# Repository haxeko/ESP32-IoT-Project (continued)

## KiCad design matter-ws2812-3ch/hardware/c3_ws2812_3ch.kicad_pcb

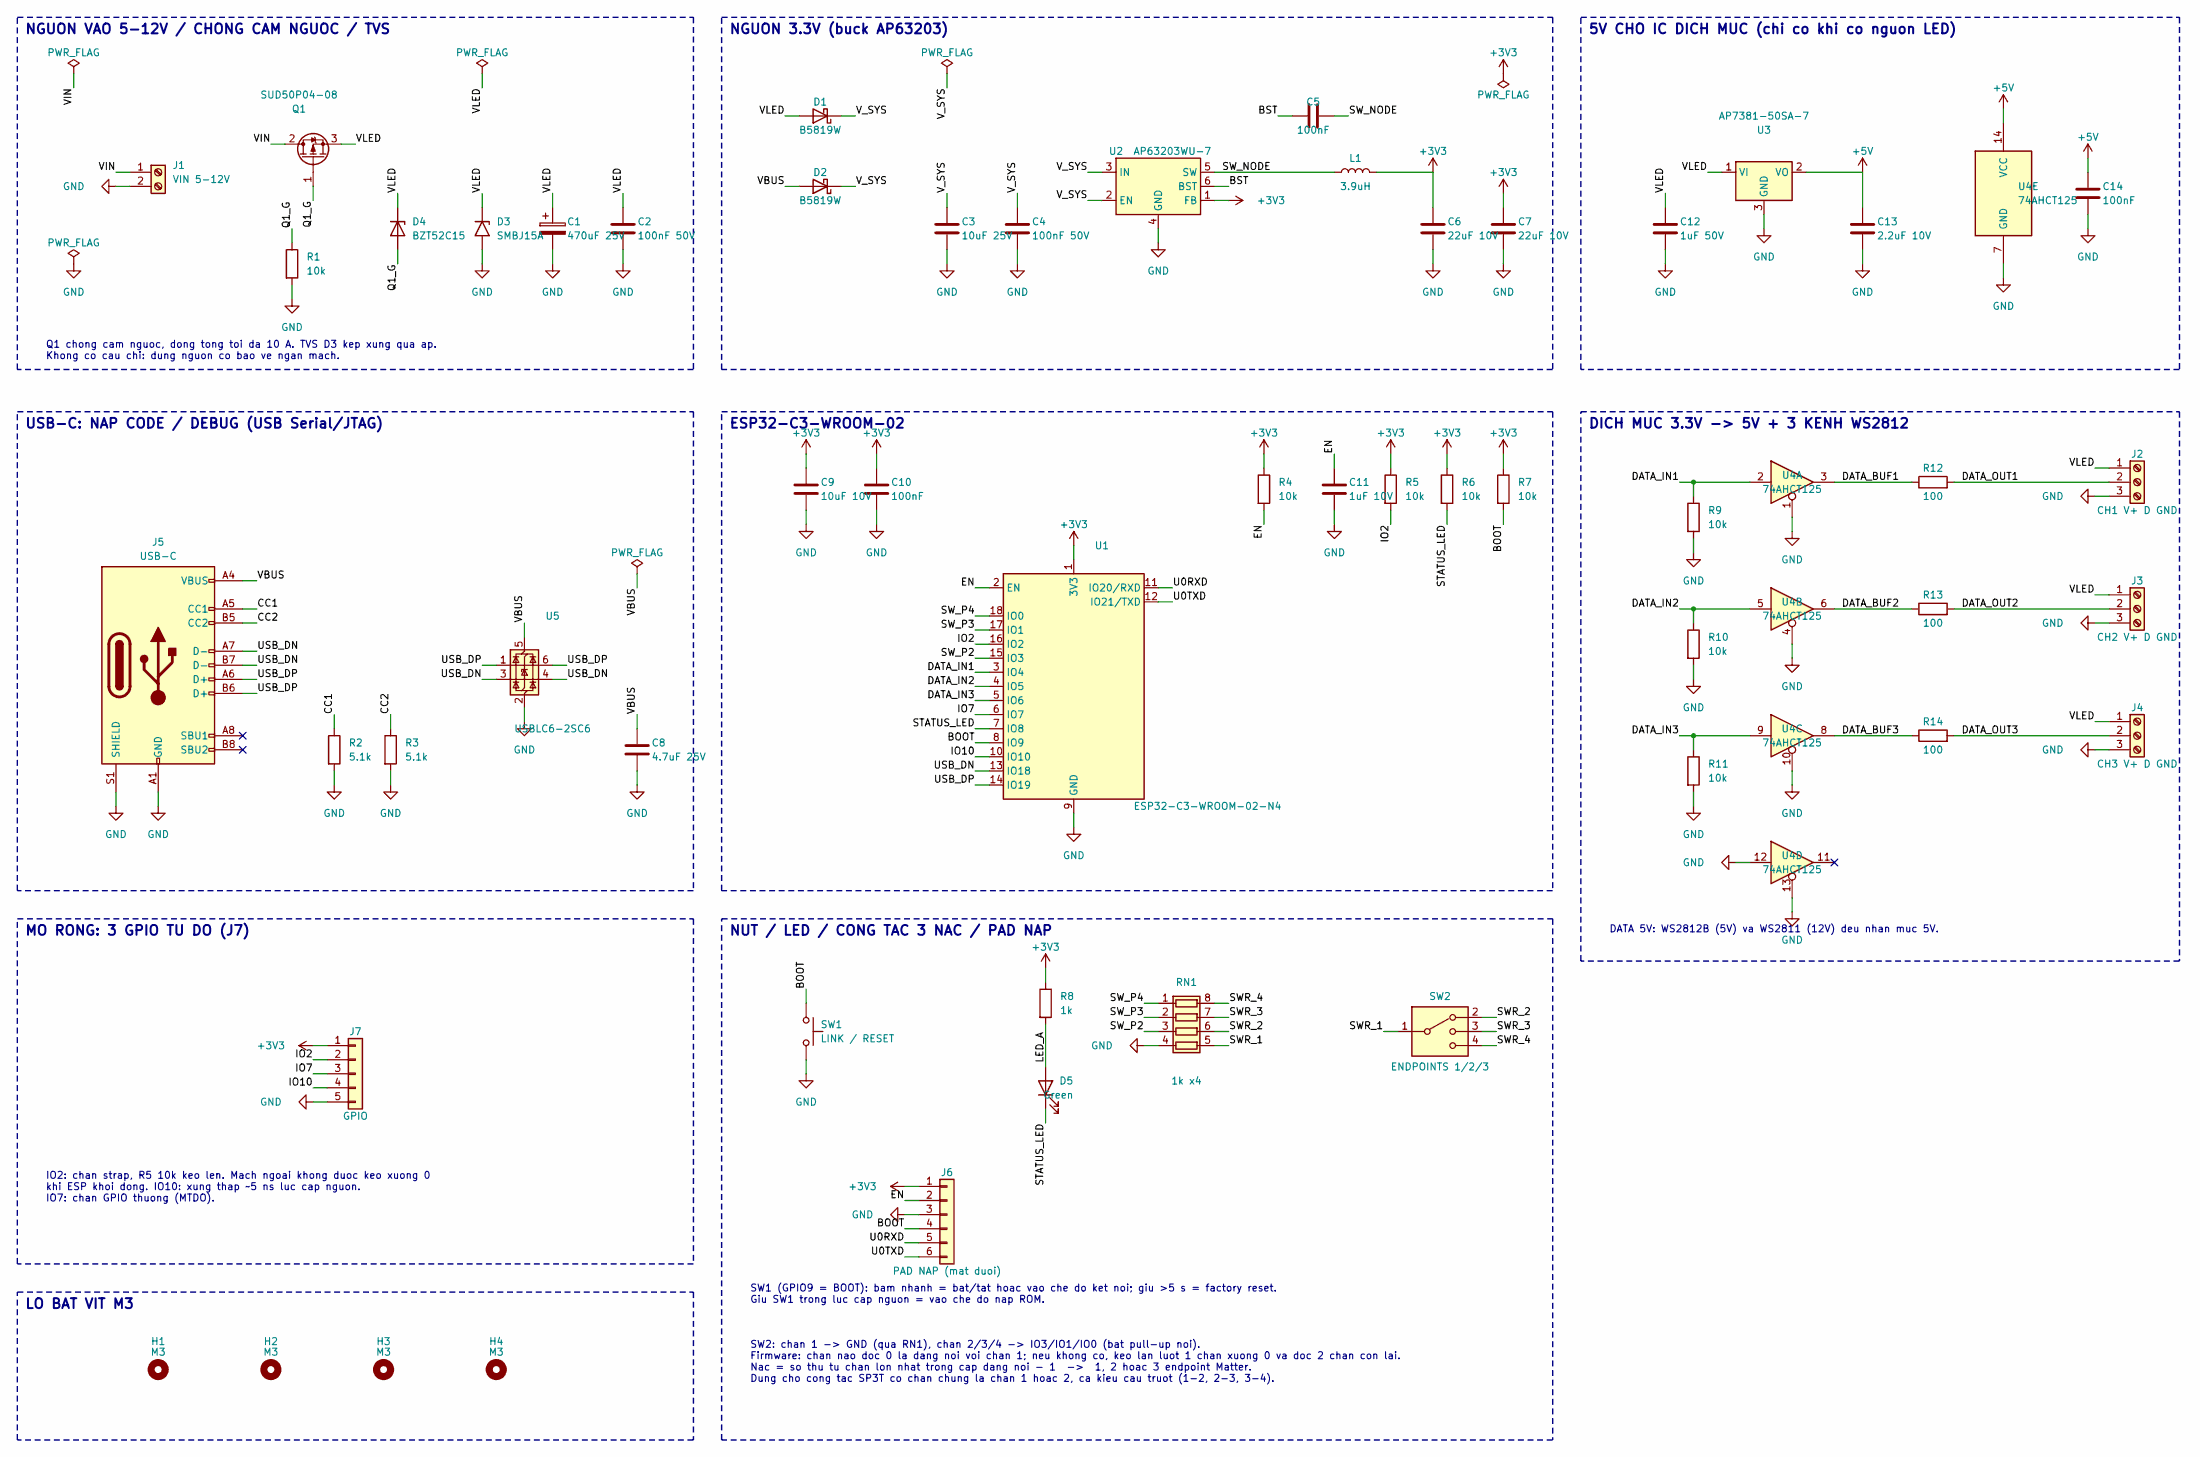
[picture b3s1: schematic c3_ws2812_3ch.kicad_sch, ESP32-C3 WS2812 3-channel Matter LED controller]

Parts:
C1: 470uF 25V; CP_Elec_10x10.5; MPN 470uF 25V 10x10.5 SMD electrolytic
C2, C4: 100nF 50V; C_0603_1608Metric; MPN MLCC 100nF 50V; LCSC C14663
C3: 10uF 25V; C_1206_3216Metric; MPN MLCC 10uF 25V
C5, C10, C14: 100nF; C_0603_1608Metric; MPN MLCC 100nF; LCSC C14663
C6, C7: 22uF 10V; C_0805_2012Metric; MPN MLCC 22uF 10V
C8: 4.7uF 25V; C_0805_2012Metric; MPN MLCC 4.7uF 25V
C9: 10uF 10V; C_0805_2012Metric; MPN MLCC 10uF 10V
C11: 1uF 10V; C_0603_1608Metric; MPN MLCC 1uF 10V
C12: 1uF 50V; C_0805_2012Metric; MPN MLCC 1uF 50V
C13: 2.2uF 10V; C_0603_1608Metric; MPN MLCC 2.2uF 10V
D1, D2: B5819W; D_SOD-123; MPN B5819W; LCSC C8598
D3: SMBJ15A; D_SMB; MPN SMBJ15A
D4: BZT52C15; D_SOD-123; MPN BZT52C15
D5: Green; LED_0603_1608Metric; MPN LED 0603 green; LCSC C72043
H1, H2, H3, H4: M3; MountingHole_3.2mm_M3
J1: VIN 5-12V; TerminalBlock_Phoenix_MKDS-1,5-2-5.08_1x02_P5.08mm_Horizont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; MPN Terminal block 2P 5.08mm (KF128-2P / MK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
J2: CH1 V+ D GND; TerminalBlock_Phoenix_MKDS-1,5-3-5.08_1x03_P5.08mm_Horizont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; MPN Terminal block 3P 5.08mm (KF128-3P / MK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
J3: CH2 V+ D GND; TerminalBlock_Phoenix_MKDS-1,5-3-5.08_1x03_P5.08mm_Horizont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; MPN Terminal block 3P 5.08mm (KF128-3P / MK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
J4: CH3 V+ D GND; TerminalBlock_Phoenix_MKDS-1,5-3-5.08_1x03_P5.08mm_Horizont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; MPN Terminal block 3P 5.08mm (KF128-3P / MK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
J5: USB-C; USB_C_Receptacle_HRO_TYPE-C-31-M-12; MPN HRO TYPE-C-31-M-12; LCSC C165948
J6: PAD NAP (mat duoi); ProgPads_1x06_P2.54mm_D1.5mm_SMD; MPN (pads on the bottom side, nothing to mo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
J7: GPIO; PinHeader_1x05_P2.54mm_Vertical; MPN Pin header 1x5 2.54mm
L1: 3.9uH; L_Sunlord_SWPA4030S; MPN SWPA4030S3R9MT
Q1: SUD50P04-08; TO-252-2; MPN SUD50P04-08-GE3 (alt. AOD4185)
R1, R4, R5, R6, R7, R9, R10, R11: 10k; R_0603_1608Metric; MPN 0603 1% 10k; LCSC C25804
R2, R3: 5.1k; R_0603_1608Metric; MPN 0603 1% 5.1k; LCSC C23186
R8: 1k; R_0603_1608Metric; MPN 0603 1% 1k; LCSC C21190
R12, R13, R14: 100; R_0603_1608Metric; MPN 0603 1% 100; LCSC C22775
RN1: 1k x4; R_Array_Convex_4x0603; MPN 4D03WGJ0102T5E (1k x4 0603 array)
SW1: LINK / RESET; SW_PUSH_6mm_H5mm; MPN Tactile 6x6mm THT, H=5mm
SW2: ENDPOINTS 1/2/3; SW_Slide_SP3T_SameSky_SLW-156646-5A-N-D; MPN Same Sky SLW-156646-5A-N-D (SP3T, 4 pin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
U1: ESP32-C3-WROOM-02-N4; ESP32-C3-WROOM-02_ThermalVia0.3; MPN ESP32-C3-WROOM-02-N4
U2: AP63203WU-7; TSOT-23-6; MPN AP63203WU-7; LCSC C780769
U3: AP7381-50SA-7; SOT-23; MPN AP7381-50SA-7
U4: 74AHCT125; SOIC-14_3.9x8.7mm_P1.27mm; MPN SN74AHCT125DR
U5: USBLC6-2SC6; SOT-23-6; MPN USBLC6-2SC6; LCSC C7519

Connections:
+3V3: C6.1, C7.1, C9.1, C10.1, J6.1, J7.1, L1.2, R4.1, R5.1, R6.1, R7.1, R8.1, U1.1 (3V3), U2.1 (FB)
+5V: C13.1, C14.1, U3.2 (VO), U4.14 (VCC)
/BOOT: J6.4, R7.2, SW1.1, U1.8 (IO9)
/BST: C5.1, U2.6 (BST)
/CC1: J5.A5 (CC1), R2.1
/CC2: J5.B5 (CC2), R3.1
/DATA_BUF1: R12.1, U4.3
/DATA_BUF2: R13.1, U4.6
/DATA_BUF3: R14.1, U4.8
/DATA_IN1: R9.1, U1.3 (IO4), U4.2
/DATA_IN2: R10.1, U1.4 (IO5), U4.5
/DATA_IN3: R11.1, U1.5 (IO6), U4.9
/DATA_OUT1: J2.2, R12.2
/DATA_OUT2: J3.2, R13.2
/DATA_OUT3: J4.2, R14.2
/EN: C11.1, J6.2, R4.2, U1.2 (EN)
/IO2: J7.2, R5.2, U1.16 (IO2)
/IO7: J7.3, U1.6 (IO7)
/IO10: J7.4, U1.10 (IO10)
/LED_A: D5.2 (A), R8.2
/Q1_G: D4.2 (A), Q1.1 (G), R1.1
/STATUS_LED: D5.1 (K), R6.2, U1.7 (IO8)
/SWR_1: RN1.5 (R4.2), SW2.1
/SWR_2: RN1.6 (R3.2), SW2.2
/SWR_3: RN1.7 (R2.2), SW2.3
/SWR_4: RN1.8 (R1.2), SW2.4
/SW_NODE: C5.2, L1.1, U2.5 (SW)
/SW_P2: RN1.3 (R3.1), U1.15 (IO3)
/SW_P3: RN1.2 (R2.1), U1.17 (IO1)
/SW_P4: RN1.1 (R1.1), U1.18 (IO0)
/U0RXD: J6.5, U1.11 (IO20/RXD)
/U0TXD: J6.6, U1.12 (IO21/TXD)
/USB_DN: J5.A7 (D-), J5.B7 (D-), U1.13 (IO18), U5.3 (I/O2), U5.4 (I/O2)
/USB_DP: J5.A6 (D+), J5.B6 (D+), U1.14 (IO19), U5.1 (I/O1), U5.6 (I/O1)
/VBUS: C8.1, D2.2 (A), J5.A4 (VBUS), J5.A9 (VBUS), J5.B4 (VBUS), J5.B9 (VBUS), U5.5 (VBUS)
/VIN: J1.1, Q1.2 (D)
/VLED: C1.1, C2.1, C12.1, D1.2 (A), D3.1 (A1), D4.1 (K), J2.1, J3.1, J4.1, Q1.3 (S), U3.1 (VI)
/V_SYS: C3.1, C4.1, D1.1 (K), D2.1 (K), U2.2 (EN), U2.3 (IN)
GND: C1.2, C2.2, C3.2, C4.2, C6.2, C7.2, C8.2, C9.2, C10.2, C11.2, C12.2, C13.2, C14.2, D3.2 (A2), J1.2, J2.3, J3.3, J4.3, J5.A1 (GND), J5.A12 (GND), J5.B1 (GND), J5.B12 (GND), J5.S1 (SHIELD), J6.3, J7.5, R1.2, R2.2, R3.2, R9.2, R10.2, R11.2, RN1.4 (R4.1), SW1.2, U1.9 (GND), U1.19 (GND), U2.4 (GND), U3.3 (GND), U4.1, U4.4, U4.7 (GND), U4.10, U4.12, U4.13, U5.2 (GND)

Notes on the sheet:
NGUON VAO 5-12V / CHONG CAM NGUOC / TVS
NGUON 3.3V (buck AP63203)
5V CHO IC DICH MUC (chi co khi co nguon LED)
USB-C: NAP CODE / DEBUG (USB Serial/JTAG)
ESP32-C3-WROOM-02
DICH MUC 3.3V -> 5V + 3 KENH WS2812
MO RONG: 3 GPIO TU DO (J7)
LO BAT VIT M3
NUT / LED / CONG TAC 3 NAC / PAD NAP
SW1 (GPIO9 = BOOT): bam nhanh = bat/tat hoac vao che do ket noi; giu >5 s = factory reset. Giu SW1 trong luc cap nguon = vao che do nap ROM.
SW2: chan 1 -> GND (qua RN1), chan 2/3/4 -> IO3/IO1/IO0 (bat pull-up noi). Firmware: chan nao doc 0 la dang noi voi chan 1; neu khong co, keo lan luot 1 chan xuong 0 va doc 2 chan con lai. Nac = so thu tu chan lon nhat trong cap dang noi - 1 -> 1, 2 hoac 3 endpoint Matter. Dung cho cong tac SP3T co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
Q1 chong cam nguoc, dong tong toi da 10 A. TVS D3 kep xung qua ap. Khong co cau chi: dung nguon co bao ve ngan mach.
DATA 5V: WS2812B (5V) va WS2811 (12V) deu nhan muc 5V.
IO2: chan strap, R5 10k keo len. Mach ngoai khong duoc keo xuong 0 khi ESP khoi dong. IO10: xung thap ~5 ns luc cap nguon. IO7: chan GPIO thuong (MTDO).

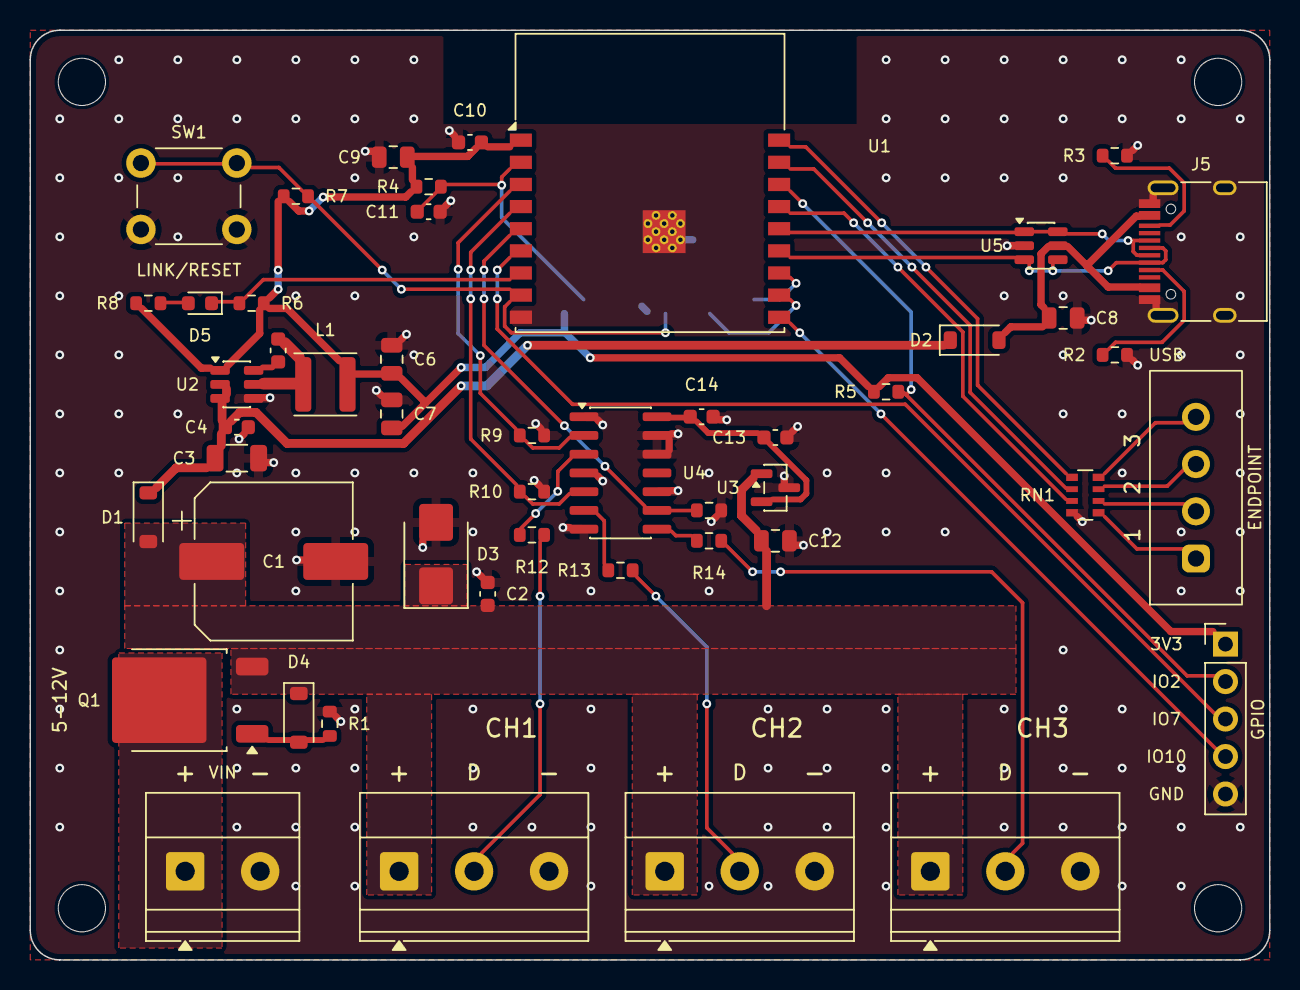
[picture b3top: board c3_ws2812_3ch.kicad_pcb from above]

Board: 2 copper layers, 84.0 x 63.0 mm, 54 parts (1 on the bottom side), 39 nets.

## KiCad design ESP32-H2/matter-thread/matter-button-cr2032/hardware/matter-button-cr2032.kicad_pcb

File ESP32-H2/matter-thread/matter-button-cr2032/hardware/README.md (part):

# PCB KiCad: nút nhấn Matter CR2032 (ESP32-H2-WROOM-02C)

Dự án KiCad 9 của mạch trong [README chính](../README.md) (mục 2–4): schematic, PCB 2 lớp đã đi dây, file sản xuất. Mọi file được sinh bằng các script trong `scripts/` từ một nguồn dữ liệu duy nhất (`scripts/design.py`), rồi kiểm tra bằng KiCad:

- **ERC: 0 lỗi, 0 cảnh báo.**
- **DRC: 0 vi phạm, 0 pad chưa nối, 0 lỗi footprint, 0 lệch giữa PCB và schematic** (`kicad-cli pcb drc --severity-all --schematic-parity`, KiCad 9.0.9).

Chưa đặt mạch, chưa đo trên bo thật: kiểm tra lại footprint module với datasheet trước khi đặt và chạy [checklist](../docs/test-checklist.md) khi có bo.

Bản không dùng module (chip ESP32-H2, thạch anh, anten in trên PCB, LED RGB WS2812B, bo 4 lớp 29,8 × 29,8 mm): [`../hardware-chip`](../hardware-chip/README.md).

| Mặt trên | Mặt dưới |
|---|---|
|  |  |

Đồng và silkscreen (mặt dưới nhìn từ dưới lên, đã lật):

## 1. File

| File | Nội dung |
|---|---|
| `matter-button-cr2032.kicad_pro/.kicad_sch/.kicad_pcb` | dự án KiCad 9 (mở bằng KiCad ≥ 9.0) |
| `lib/matter_button.kicad_sym`, `lib/matter_button.pretty/` | linh kiện riêng: symbol + footprint ESP32-H2-WROOM-02C, power symbol VBAT, đế Keystone 3034 (bản sửa) |
| `fab/matter-button-cr2032-gerber.zip` | Gerber (RS-274X, không thuộc tính X2, theo hướng dẫn KiCad của JLCPCB) + khoan Excellon: gửi thẳng cho nhà sản xuất PCB |
| `fab/bom-vi.csv` | BOM theo tên và thông số linh kiện (tiếng Việt), kèm từ khóa tìm mua, mã LCSC và linh kiện thay thế |
| `fab/bom-jlcpcb.csv`, `fab/cpl-jlcpcb.csv` | BOM (mã LCSC + MPN) và file vị trí linh kiện (tên cột theo JLCPCB) cho dịch vụ lắp ráp; không có U1, BT1 (hàn tay) |
| `fab/bom.csv` | BOM đầy đủ (MPN, mã LCSC, mô tả), C7 ghi DNP |
| `docs/schematic.pdf` | schematic KiCad |
| `docs/assembly-top.svg`, `docs/assembly-bottom.svg` | bản vẽ lắp ráp: viền linh kiện + ký hiệu (C7 gạch chéo: không lắp) |
| `docs/pcb-*.png` | ảnh render 3D (không có model linh kiện) và layout 2D |
| `scripts/` | các script sinh toàn bộ dự án (mục 6) |

## 2. Thông số bo

| Mục | Giá trị |
|---|---|
| Kích thước | **29,8 × 23,9 mm**, góc bo R0,5; anten module chìa ra 6 mm ở mép trên → cả cụm **29,8 × 29,9 mm** (dưới 30 × 30 mm); không có lỗ bắt vít |
| Lớp | 2 lớp FR-4 1,6 mm, đồng 1 oz |
| Đường mạch | 0,2 mm tín hiệu, 0,3 mm nguồn và GND, 0,4 mm cực + pin; khe hở 0,2 mm (tối thiểu 0,15 mm ở pad của linh kiện) |
| Via | 0,6 / 0,3 mm, phủ mask; via nhiệt trong pad GND của module theo land pattern datasheet |
| Cách mép bo | đồng ≥ 0,3 mm |
| Bề mặt | **ENIG** khuyến nghị: pad tiếp xúc âm của pin là đồng trần, chân WSON bước 0,5 mm |
| GND | phủ đồng cả hai mặt (trừ vành quanh mép pin ở mặt dưới), mỗi pad GND có via riêng xuống pad tiếp xúc âm của pin hoặc mặt phẳng dưới; module nối mặt dưới qua 6 via nhiệt của pad 29 |
| Linh kiện | mặt trên tất cả, trừ đế pin BT1 ở mặt dưới; 10 pad test ở mặt dưới |

Các thông số nằm trong quy trình tiêu chuẩn của JLCPCB / PCBWay (track/space 0,127 mm, lỗ 0,3 mm), không cần tùy chọn đặc biệt.

## 3. Bố trí

| Vùng | Linh kiện | Lý do |
|---|---|---|
| Mép trên, sát mép phải | U1 ESP32-H2-WROOM-02C, vùng anten 6 mm **nhô ra ngoài mép bo** | không đồng, không FR-4 dưới anten (datasheet WROOM-02C mục 11, ESP32-H2 Hardware Design Guidelines); mặt phẳng GND chạy tới sát mép, đúng chân anten |
| Trái module | C6 100 nF sát chân 1; R4 (+ C7 không lắp) ở EN; C8, R7, R6 (nút: lọc RC, kéo lên 1 MΩ) ở GPIO10; R5 kéo lên GPIO8 | trục 3V3 chạy dọc mép trái từ JP2 lên chân 1, nhánh x = 6,5 mm cho các điện trở kéo lên; đường nút đi trong lề trái của module (giữa hàng chân và vùng cấm dưới module) xuống SW1 |
| Phải module | không có linh kiện (module sát mép phải) | UART, USB và đo pin đổi lớp ngay cạnh chân module, xuống pad test ở mặt dưới |
| Dưới module | SW1 PTS810 ở giữa bo, C2 dưới nút; LED D1 + R8 (GPIO22) bên phải nút | đặt ống dẫn sáng ở tọa độ D1 |
| Góc dưới trái | TPS63900: R1–R3 phía trên, C4 (VOUT) bên trái, C3 (VIN) bên phải, L1 phía dưới; C5, JP2 sát mép trái | vòng VIN và VOUT ngắn trên lớp trên, cuộn cảm sát LX1/LX2 |
| Góc dưới phải | Q1, JP1, C1; R9 1 MΩ + C9 100 nF đo pin ở góc | chuỗi nguồn phải → trái: tai + của đế pin → Q1 → JP1 → C1 → đường VBAT dọc mép dưới → C2, C3/U2 → C4 → JP2 → 3V3 |
| Mặt dưới | đế pin Keystone 3034 nằm dưới module và mạch; mép pin cách mép dưới 0,54 mm, cách chân anten 3,4 mm | pad tiếp xúc âm Ø17,8 mm là một phần GND; vành 8,95–10,3 mm quanh tâm pin không có đồng (mép vỏ pin là cực +) |
| Mặt dưới, ngoài đế pin | 10 pad test Ø1,5 mm: hai nhóm 2 × 2 ở hai góc trên (bước 2,54 × 2,7 mm), RX và VBAT bên phải đế pin; chữ "Made by Haxeko" và số rev ở dải giữa mép trên | kẹp pogo-pin; nhãn in ở mặt dưới; đường VBAT_SENSE đi dọc mép phải ở mặt dưới |

Chữ in mặt trên: "Thread Button" (dọc mép trái), U1, JP1, JP2. Mặt dưới: "Made by Haxeko", rev, nhãn pad test, dấu + ở tai dương của đế pin.

Tọa độ (mm, gốc ở góc trên trái, nhìn từ mặt trên; nhìn từ mặt dưới thì trái/phải đảo lại) để thiết kế vỏ và jig:

| Vật | Tọa độ |
|---|---|
| Tâm nút SW1 (thân 4,2 × 3,2 mm) | (14,9; 17,4) |
| Tâm LED D1 | (19,4; 16,8) |
| Tâm đế pin BT1 (mặt dưới) | (14,9; 13,36); pin Ø20 mm từ y = 3,36 tới 23,36 |
| Pad test, góc trên trái | y = 1,6: x = 2,00 GND · 4,54 3V3; y = 4,3: x = 2,00 BOOT · 4,54 EN |
| Pad test, góc trên phải | y = 1,6: x = 25,44 TXD0 · 27,98 VBAT_SENSE; y = 4,3: x = 25,44 USB D− · 27,98 USB D+ |
| Pad test, bên phải đế pin | RXD0 (26,9; 18,5) · VBAT (27,2; 21,2) |
| Cầu hàn đo dòng JP1 / JP2 | (24,0; 17,2) / (1,65; 18,62) |
| Module | thân x = 11 … 29, y = −6 … 14; mép anten y = −6, chân anten y = 0 (mép bo) |

Chiều cao: module 3,2 mm trên bo 1,6 mm; chiều cao nút PTS810 và đế pin Keystone 3034 lấy theo datasheet của chúng. Trong vỏ: không đặt kim loại (vít, lò xo, tấm che) trong ~15 mm quanh anten; kiểm tra RSSI/LQI của parent khi đã đóng vỏ (checklist mục C).

**Đánh đổi của bo nhỏ:** để cả cụm (tính anten) dưới 30 × 30 mm, bo chỉ cao 23,9 mm nên pin chỉ còn cách chân anten 3,4 mm (bố trí 25 × 27 mm: 6,5 mm; 30 × 38 mm: ~16 mm). Pin nằm sau mặt phẳng GND, không nằm dưới anten, nhưng Espressif khuyến nghị khoảng trống ~15 mm quanh anten, nên tầm phủ có thể giảm. Đo RSSI/LQI trước khi làm vỏ; nếu yếu, dùng lại bố trí 25 × 27 mm (commit `af26218`) hoặc 30 × 38 mm (commit `6649456`), cùng schematic.

## 4. Đặt mạch và lắp ráp

1. **PCB**: tải `fab/matter-button-cr2032-gerber.zip` lên JLCPCB/PCBWay: 2 lớp, 1,6 mm, ENIG, các mục khác để mặc định.
2. **Lắp ráp JLCPCB (tùy chọn)**: chọn lắp mặt trên (Top side), tải `fab/bom-jlcpcb.csv` và `fab/cpl-jlcpcb.csv`. Mỗi dòng BOM đã có mã LCSC nên được ghép tự động: 10 loại Basic, 5 loại Extended (U2 C1518762, L1 C391305, C1/C2 C469553, R1 C49010116, SW1 C116501; phí nạp tính theo loại). Nếu JLCPCB báo hết hàng: tụ C1/C2 thay bằng Samsung CL32A227MQVNNNE (C400951); SW1 phải là bản **SJM** (160 gf), đừng để trang ghép tự chọn bản SJG (C221895, 400 gf). Kiểm tra góc xoay ở bản xem trước (nhất là U2, Q1, D1, L1, SW1: chấm chân 1 và cực LED). C7 không lắp (DNP).
   - **U1 và BT1 không có ở LCSC** nên không có trong hai file trên: hàn tay sau khi nhận bo. BT1: 2 tai lớn ở mặt dưới, dễ hàn. U1: pad ở mép module hàn bằng mỏ hàn; pad GND giữa (29) có 6 via nhiệt, hàn từ mặt dưới qua via (hoặc khò/bếp gia nhiệt với kem hàn). Muốn JLCPCB lắp U1 thì dùng Global Sourcing hoặc gửi linh kiện (consigned) rồi thêm dòng U1 vào BOM/CPL.
3. **JP1, JP2** là cầu hàn đã nối sẵn bằng đồng: cắt đường đồng nhỏ giữa hai pad để đo dòng (nối ampe kế vào hai pad), đo xong hàn nối lại.
4. Cấp nguồn lần đầu, nạp firmware: [README chính mục 8.3](../README.md#83-nạp-firmware) và [checklist](../docs/test-checklist.md). Khi có pin, **không** cấp 3V3 vào pad 3V3.

## 5. Ghi chú thiết kế

- **Footprint ESP32-H2-WROOM-02C** tự vẽ theo land pattern datasheet v1.2 mục 11.1: pad 1,5 × 0,9 mm bước 1,5 mm; chân 1–9 trái, 10–19 dưới, 20–28 phải; pad GND 29 gồm hai phần 2,8 × 0,55 và 2,8 × 1,6 mm với 6 via nhiệt (phủ mask mặt dưới). Gốc tọa độ là tâm module, vùng anten y = −10 … −4 có keep-out mọi lớp đồng. Silkscreen chỉ vẽ góc dưới và chấm chân 1 (vùng anten nằm ngoài bo).
- **TPS63900**: symbol chuẩn của KiCad đã có chân 11 (pad tản nhiệt) ẩn, chồng lên chân GND 8. Footprint WSON-10 không có via trong pad (TI: via là tùy chọn); pad tản nhiệt nối chân 8 bằng đường mạch, rồi ra hai via GND hai bên.
- **Keystone 3034**: footprint chuẩn có hai pad cùng số "1" (hai tai của cùng một lá kim loại); KiCad 9 sẽ đòi nối đồng giữa chúng vòng qua pin. Bản trong `lib/` bỏ số của tai trái (nhìn từ trên), tai này chỉ để hàn giữ.
- **Ký hiệu linh kiện** trên silkscreen chỉ có U1, JP1, JP2 (bo quá dày cho chữ); vị trí từng linh kiện xem `docs/assembly-*.svg`.
- **Đi dây**: mọi đường trừ GND được vẽ trong script (khóa): phần TPS63900 bước 0,5 mm, đường nguồn (cực + pin, VBAT, 3V3), nút nhấn, LED, đo pin, UART/USB và các đường xuống pad test ở mặt dưới. FreeRouting chỉ chạy khi còn kết nối chưa đi (bố trí này: không còn, bước `route` bỏ qua nó). GND không qua autorouter: phủ đồng hai mặt nối tất cả.
- **Dưới pin**: mặt dưới chỉ đi dây trong phần không bị pin che (hai góc trên và hai dải bên); vành quanh mép pin là vùng cấm (rule area: không đường mạch, không via, không phủ đồng) vì mép vỏ CR2032 là cực + và cọ vào bo khi lắp pin. Via GND chỉ đặt bên trong pad tiếp xúc âm hoặc ngoài pin.

## 6. Sinh lại dự án từ script

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
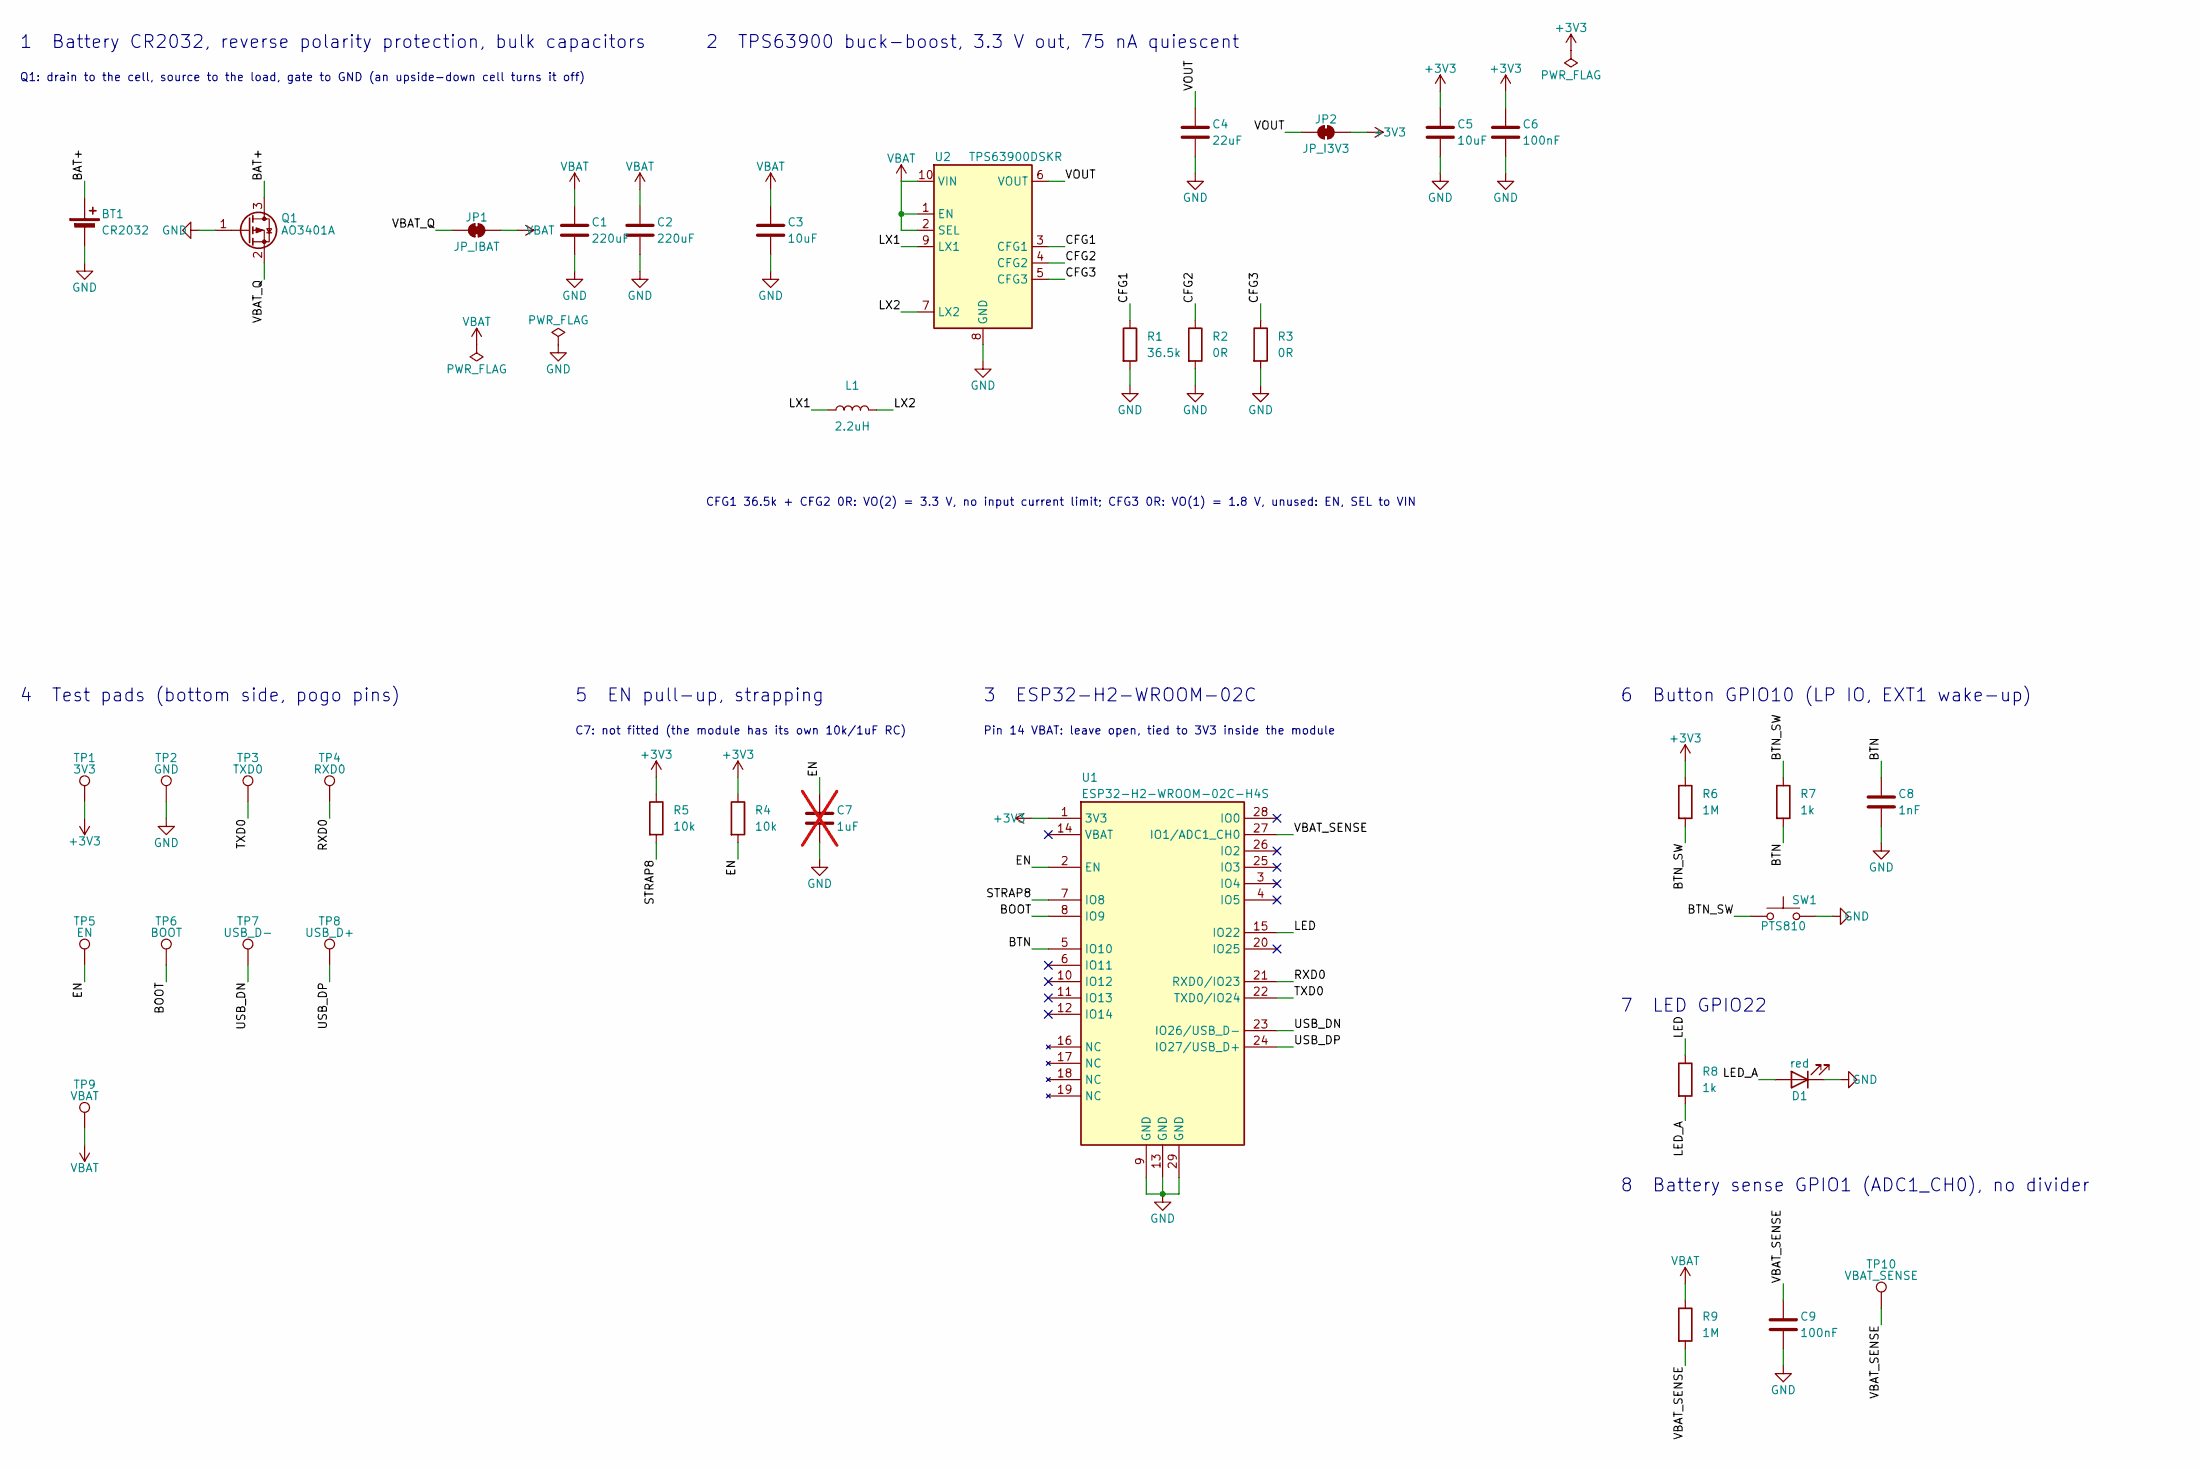
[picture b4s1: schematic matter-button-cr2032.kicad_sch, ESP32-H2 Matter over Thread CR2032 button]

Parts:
BT1: CR2032; BatteryHolder_Keystone_3034_CR2032; MPN Keystone 3034
C1, C2: 220uF; C_1210_3225Metric; MPN GRM32ER60J227ME05L; LCSC C469553
C3, C5: 10uF; C_0603_1608Metric; MPN CL10A106KP8NNNC; LCSC C19702
C4: 22uF; C_0603_1608Metric; MPN CL10A226MQ8NRNC; LCSC C59461
C6, C9: 100nF; C_0402_1005Metric; MPN CL05B104KO5NNNC; LCSC C1525
C7: 1uF; C_0402_1005Metric; MPN CL05A105KA5NQNC; LCSC C52923; not fitted
C8: 1nF; C_0402_1005Metric; MPN CL05B102KB5NNNC; LCSC C1523
D1: red; LED_0603_1608Metric; MPN KT-0603R; LCSC C2286
JP1: JP_IBAT; SolderJumper-2_P1.3mm_Bridged_RoundedPad1.0x1.5mm
JP2: JP_I3V3; SolderJumper-2_P1.3mm_Bridged_RoundedPad1.0x1.5mm
L1: 2.2uH; L_1008_2520Metric; MPN DFE252012P-2R2M=P2; LCSC C391305
Q1: AO3401A; SOT-23; MPN AO3401A; LCSC C15127
R1: 36.5k; R_0402_1005Metric; MPN FRC0402F3652TS; LCSC C49010116
R2, R3: 0R; R_0402_1005Metric; MPN 0402WGF0000TCE; LCSC C17168
R4, R5: 10k; R_0402_1005Metric; MPN 0402WGF1002TCE; LCSC C25744
R6, R9: 1M; R_0402_1005Metric; MPN 0402WGF1004TCE; LCSC C26083
R7, R8: 1k; R_0402_1005Metric; MPN 0402WGF1001TCE; LCSC C11702
SW1: PTS810; SW_SPST_PTS810; MPN PTS810 SJM 250 SMTR LFS; LCSC C116501
TP1: 3V3; TestPoint_Pad_D1.5mm
TP2: GND; TestPoint_Pad_D1.5mm
TP3: TXD0; TestPoint_Pad_D1.5mm
TP4: RXD0; TestPoint_Pad_D1.5mm
TP5: EN; TestPoint_Pad_D1.5mm
TP6: BOOT; TestPoint_Pad_D1.5mm
TP7: USB_D-; TestPoint_Pad_D1.5mm
TP8: USB_D+; TestPoint_Pad_D1.5mm
TP9: VBAT; TestPoint_Pad_D1.5mm
TP10: VBAT_SENSE; TestPoint_Pad_D1.5mm
U1: ESP32-H2-WROOM-02C-H4S; ESP32-H2-WROOM-02C; MPN ESP32-H2-WROOM-02C-H4S
U2: TPS63900DSKR; WSON-10-1EP_2.5x2.5mm_P0.5mm_EP1.2x2mm; MPN TPS63900DSKR; LCSC C1518762

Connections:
+3V3: C5.1, C6.1, JP2.2 (B), R4.1, R5.1, R6.1, TP1.1, U1.1 (3V3)
/BAT+: BT1.1 (+), Q1.3 (D)
/BOOT: TP6.1, U1.8 (IO9)
/BTN: C8.1, R7.2, U1.5 (IO10)
/BTN_SW: R6.2, R7.1, SW1.1
/CFG1: R1.1, U2.3 (CFG1)
/CFG2: R2.1, U2.4 (CFG2)
/CFG3: R3.1, U2.5 (CFG3)
/EN: C7.1, R4.2, TP5.1, U1.2 (EN)
/LED: R8.1, U1.15 (IO22)
/LED_A: D1.2 (A), R8.2
/LX1: L1.1, U2.9 (LX1)
/LX2: L1.2, U2.7 (LX2)
/RXD0: TP4.1, U1.21 (RXD0/IO23)
/STRAP8: R5.2, U1.7 (IO8)
/TXD0: TP3.1, U1.22 (TXD0/IO24)
/USB_DN: TP7.1, U1.23 (IO26/USB_D-)
/USB_DP: TP8.1, U1.24 (IO27/USB_D+)
/VBAT_Q: JP1.1 (A), Q1.2 (S)
/VBAT_SENSE: C9.1, R9.2, TP10.1, U1.27 (IO1/ADC1_CH0)
/VOUT: C4.1, JP2.1 (A), U2.6 (VOUT)
GND: BT1.2 (-), C1.2, C2.2, C3.2, C4.2, C5.2, C6.2, C7.2, C8.2, C9.2, D1.1 (K), Q1.1 (G), R1.2, R2.2, R3.2, SW1.2, TP2.1, U1.9 (GND), U1.13 (GND), U1.29 (GND), U2.8 (GND), U2.11 (GND)
VBAT: C1.1, C2.1, C3.1, JP1.2 (B), R9.1, TP9.1, U2.1 (EN), U2.2 (SEL), U2.10 (VIN)

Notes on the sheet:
1 Battery CR2032, reverse polarity protection, bulk capacitors
Q1: drain to the cell, source to the load, gate to GND (an upside-down cell turns it off)
2 TPS63900 buck-boost, 3.3 V out, 75 nA quiescent
CFG1 36.5k + CFG2 0R: VO(2) = 3.3 V, no input current limit; CFG3 0R: VO(1) = 1.8 V, unused: EN, SEL to VIN
4 Test pads (bottom side, pogo pins)
5 EN pull-up, strapping
C7: not fitted (the module has its own 10k/1uF RC)
3 ESP32-H2-WROOM-02C
Pin 14 VBAT: leave open, tied to 3V3 inside the module
6 Button GPIO10 (LP IO, EXT1 wake-up)
7 LED GPIO22
8 Battery sense GPIO1 (ADC1_CH0), no divider

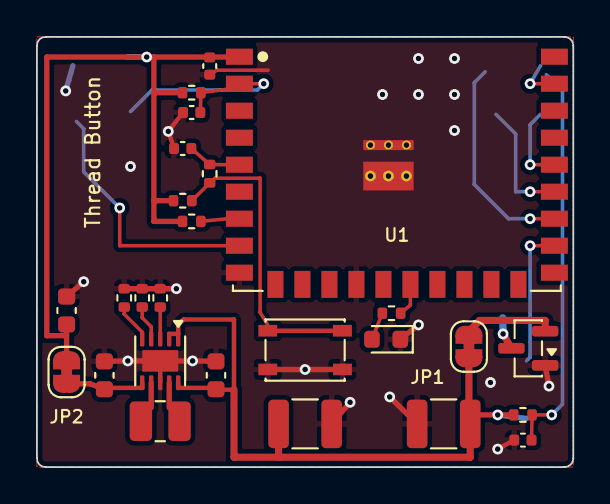
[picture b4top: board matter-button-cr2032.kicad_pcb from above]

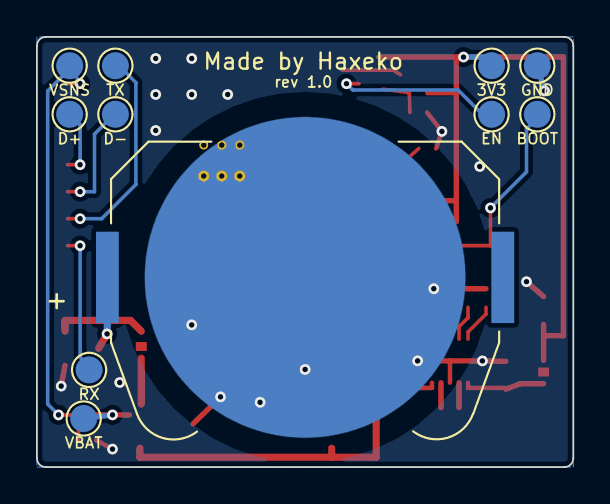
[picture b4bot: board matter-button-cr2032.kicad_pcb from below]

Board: 2 copper layers, 29.8 x 23.9 mm, 37 parts (11 on the bottom side), 23 nets.

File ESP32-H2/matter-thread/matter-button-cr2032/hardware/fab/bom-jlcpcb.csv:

Comment,Designator,Footprint,LCSC Part #,Manufacturer Part Number
22uF,C4,0603,C59461,CL10A226MQ8NRNC
1nF,C8,0402,C1523,CL05B102KB5NNNC
220uF,"C1,C2",1210,C469553,GRM32ER60J227ME05L
10uF,"C3,C5",0603,C19702,CL10A106KP8NNNC
100nF,"C6,C9",0402,C1525,CL05B104KO5NNNC
red,D1,0603,C2286,KT-0603R
2.2uH,L1,1008,C391305,DFE252012P-2R2M=P2
AO3401A,Q1,SOT-23,C15127,AO3401A
36.5k,R1,0402,C49010116,FRC0402F3652TS
0R,"R2,R3",0402,C17168,0402WGF0000TCE
10k,"R4,R5",0402,C25744,0402WGF1002TCE
1M,"R6,R9",0402,C26083,0402WGF1004TCE
1k,"R7,R8",0402,C11702,0402WGF1001TCE
PTS810,SW1,SMD 4.2x3.2mm tact switch,C116501,PTS810 SJM 250 SMTR LFS
TPS63900DSKR,U2,WSON-10 2.5x2.5mm,C1518762,TPS63900DSKR

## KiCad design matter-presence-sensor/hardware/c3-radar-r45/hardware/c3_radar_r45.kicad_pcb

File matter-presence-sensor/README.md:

# Matter Presence Sensor (HLK-LD2410C)

Cảm biến hiện diện chuẩn Matter (device type **Occupancy Sensor 0x0107**) dùng radar 24 GHz **HLK-LD2410C**. Một mã nguồn firmware chung cho mọi bo: cùng thuật toán, cùng quy định về tên, phiên bản, entity, khoá lưu trữ. Các bo chỉ khác nhau ở **file cấu hình bo** (chân, LED, nút, console), tức là mỗi bo một bản firmware build từ cùng mã.

| Thư mục | Nội dung |
|---|---|
| [`firmware/`](firmware) | Firmware ESP-IDF + esp-matter chung cho mọi bo, host test, script build. Hướng dẫn đầy đủ: [`firmware/README.md`](firmware/README.md) |
| [`hardware/c3-radar-r45/`](hardware/c3-radar-r45) | Mạch in KiCad của bo **c3-radar r45** (ESP32-C3-WROOM-02-N4 + LD2410C, tròn Ø45 mm): sơ đồ, PCB, gerber, BOM, ảnh render, cấu hình ESPHome cũ |
| [`.github/workflows/matter-presence-sensor.yml`](../.github/workflows/matter-presence-sensor.yml) | CI: host test, rồi build mọi bo và lưu file firmware vào Artifacts |

## Các bo

| Bo (`tools/build.sh <bo>`) | Chip, kết nối | Radar (ESP RX ← radar TX, ESP TX → radar RX) | LED | Nút | Log | Trạng thái |
|---|---|---|---|---|---|---|
| `c3-supermini` | ESP32-C3 SuperMini, Wi-Fi | GPIO3, GPIO4 | GPIO8 một màu, sáng khi mức thấp | GPIO9 (BOOT) | USB-C (USB-Serial-JTAG) | build được; firmware cũ cùng chân đã chạy trên bo |
| `c3-wroom-devkit` | ESP32-C3-WROOM-02-N4 (kiểu DevKitC-02), Wi-Fi | GPIO3, GPIO4 | WS2812 GPIO8 | GPIO9 (BOOT) | USB (USB-Serial-JTAG) | build được; cùng cấu hình biến thể `esplearn` 1.0.175 (trước đó `wroom_n4`) |
| `c3-radar-r45` | mạch [`hardware/c3-radar-r45`](hardware/c3-radar-r45), ESP32-C3-WROOM-02-N4, Wi-Fi | IO10, IO3 | không có | pad IO9 (chập xuống GND) | pad RX0 / TX0 (UART0), USB-C chỉ cấp nguồn | build được; **chưa chạy trên bo** |
| `h2-mini` | ESP32-H2 mini (ESP32-H2 SuperMini), **Thread** | GPIO11, GPIO12 | WS2812 GPIO8 | GPIO9 (BOOT) | UART0 (GPIO23/24) và USB-C | build được; chân, cấu hình Thread, PID như bản H2 cũ; **chưa chạy trên bo** |
| `h2-wroom` (ESP32-H2 WROOM) | ESP32-H2, Thread | — | — | — | — | **chưa có**: cần sơ đồ chân |

Bản ESP32-H2 trước đây vẫn ở `ESP32-H2/matter-presence-ld2410-learning` (không đổi). Bo `h2-mini` là bản đó chuyển sang mã chung: OTA từ bản cũ lên `h2-mini` giữ ghép nối (cùng PID `0x8000`, bảng phân vùng, khoá lưu trữ).

## Quy định chung

- **Firmware mặc định giống nhau cho mọi bo:** radar quyết định có người hay không; ESP32 học phòng trống 120 s và đặt ngưỡng cho radar từ mức cao nhất (`LD2410_LEARN_PEAK`, xem `firmware/README.md`). Hold time mặc định 30 s.
- **Nút và đèn:** bấm đúp mở ghép nối, bấm 3 lần học phòng trống, giữ 5 s factory reset; cùng màu đèn. Riêng bo ESP32-H2 giữ nút và đèn như bản H2 cũ (`PRESENCE_BUTTON_LED_H2`): bấm 4 lần không làm gì (bo C3: ghi ngưỡng xuất xưởng), ghi ngưỡng xuất xưởng xong thì đèn xanh lá 10 s (bo C3: tím nháy).
- **Tên, phiên bản:** Manufacturer `Haxeko`, Model `Presence LD2410`, tên thiết bị `Presence-` + 4 ký tự cuối số serial, số serial = MAC trong eFuse, phiên bản `1.0.<số commit>`.
- **Matter:** VID `0xFFF1` (test). PID **`0x8001` cho ESP32-C3 (Wi-Fi)**, **`0x8000` cho ESP32-H2 (Thread)**: giữ như các bản đã ghép nối, không đổi. Endpoint 1 Occupancy Sensor (cùng Hold time, Learn empty room), 2 Range, 3 Radar resolution, 4 Radar Bluetooth.
- **Phiên bản và OTA:** SoftwareVersion là số commit của cả repo (`git rev-list --count HEAD`), nên phải lớn hơn bản đang chạy trên bo. Khi đưa nhánh vào `main`, dùng **merge commit, không squash**: squash làm số commit nhỏ đi và bo sẽ từ chối bản OTA.
- **OTA giữa các bo:** mọi bo C3 cùng VID/PID và cùng số phiên bản, Matter Server không phân biệt được (bo H2 có PID riêng, không lẫn với C3). Chỉ cập nhật một bo bằng file có tên bo đó (`presence-<bo>-<phiên bản>.ota`). Nạp nhầm file của bo khác thì chân radar, LED, nút và cổng log sai (chưa thử trên bo): nạp lại đúng file qua USB / pad nạp.
- **Không đổi khi chưa thống nhất:** chân, giao thức radar, VID/PID, device type, endpoint, cluster, khoá NVS, bảng phân vùng, khoá và chứng chỉ.

## Build nhanh

```bash
cd matter-presence-sensor/firmware
tools/build.sh c3-wroom-devkit          # hoặc c3-supermini, c3-radar-r45, h2-mini
tools/build.sh c3-radar-r45 unique_setup  # thêm tính năng: features/<tên>.defaults
```

Cần ESP-IDF v6.0.2 + esp-matter 1.6.1 (Docker `espressif/esp-matter:release-v1.6.1_idf_v6.0.2`). Kết quả trong `firmware/dist/`. Chi tiết: mục **Build** của `firmware/README.md`.

## Nguồn gốc

- `firmware/`: bản ổn định `ESP32-C3/matter-presence-ld2410` (nhánh `claude/c3-matter-presence-rewrite`) cộng cách học phòng trống của biến thể `esplearn` 1.0.175 (nhánh `claude/c3-wroom-esp-presence`). Bộ lọc năng lượng `espfilter` không đưa sang. Các thư mục cũ `ESP32-C3/`, `ESP32-H2/` để nguyên.
- `hardware/c3-radar-r45/`: toàn bộ nội dung repo `haxeko/presence-pcb` (commit `decc513`), không kèm lịch sử; thư mục `firmware/` của repo đó (ESPHome) đổi tên thành `esphome/`.

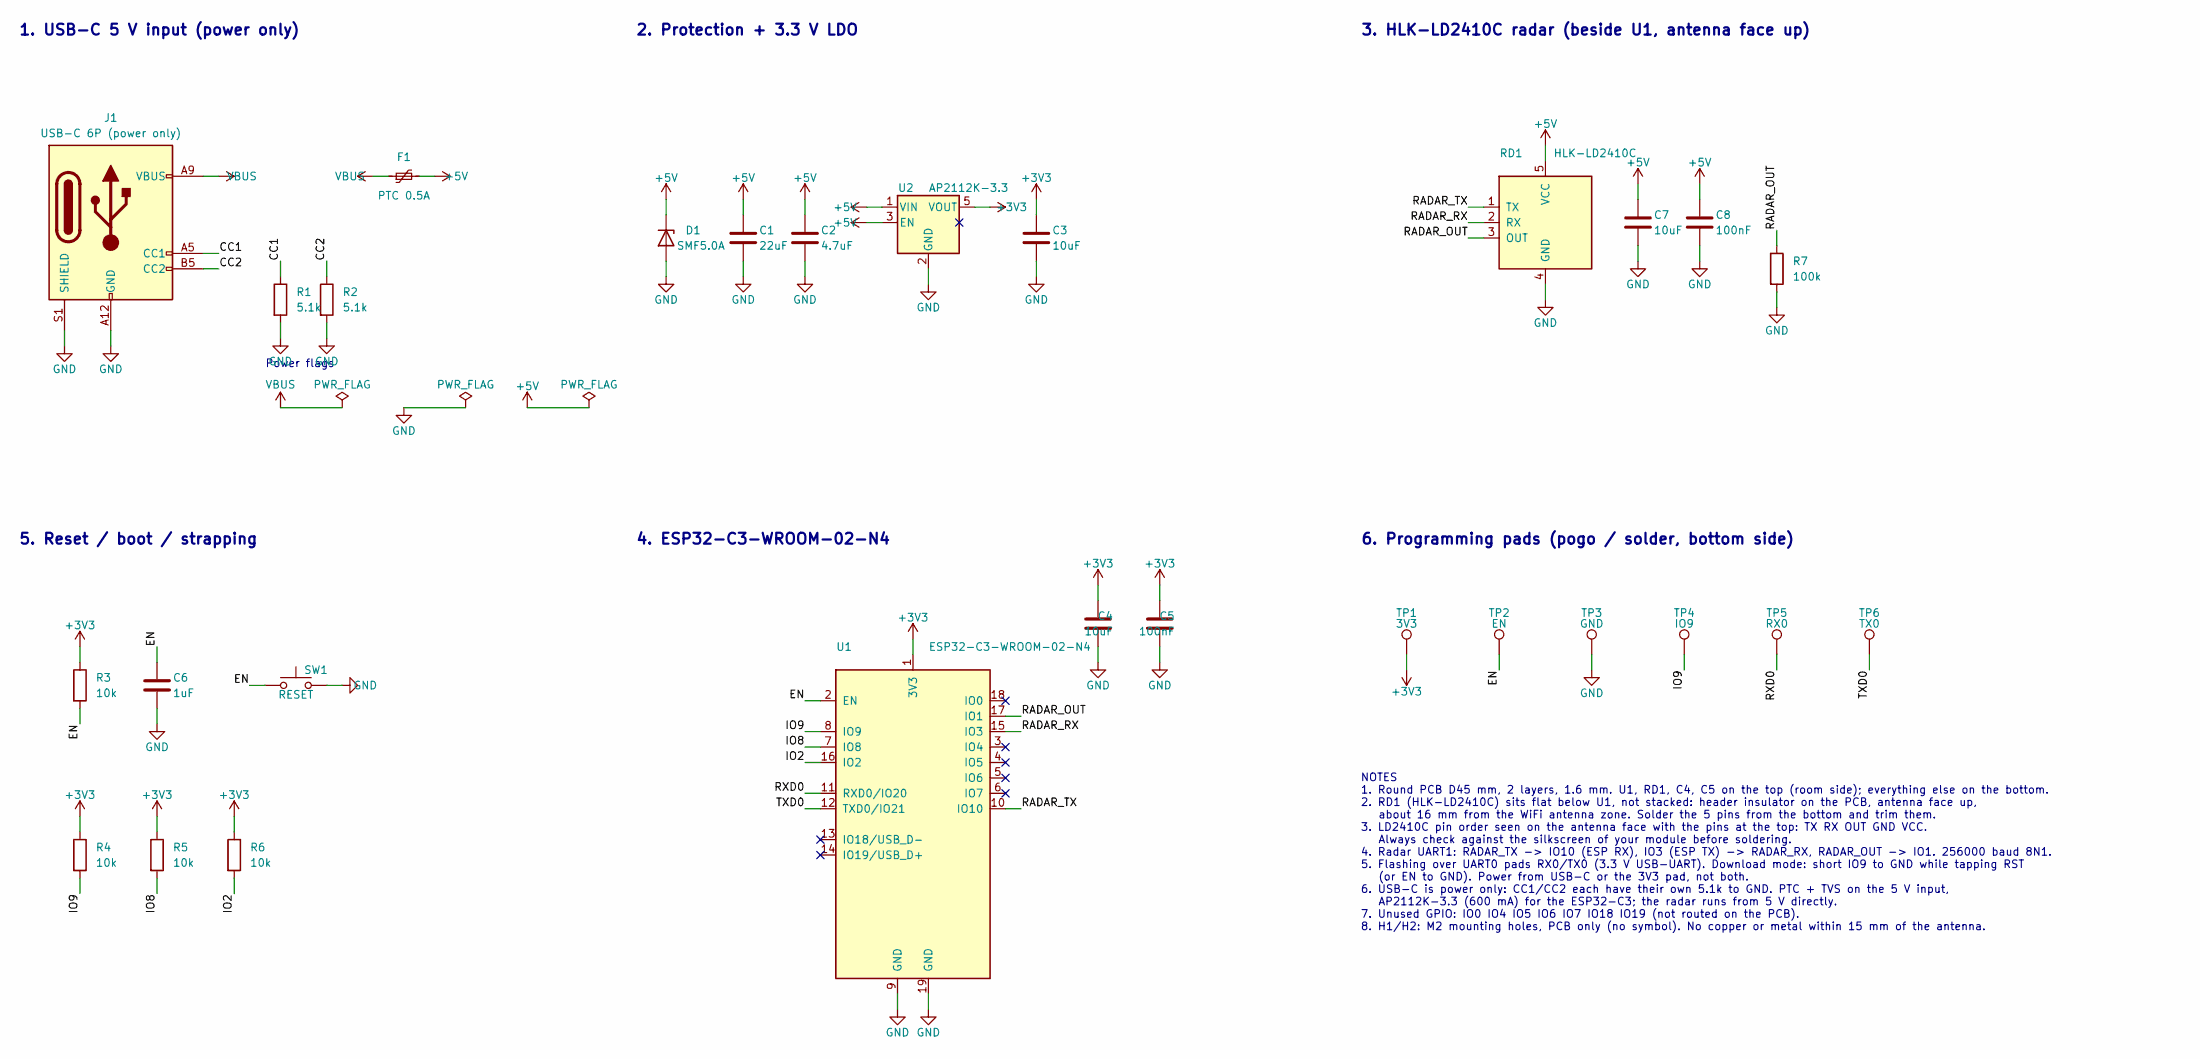
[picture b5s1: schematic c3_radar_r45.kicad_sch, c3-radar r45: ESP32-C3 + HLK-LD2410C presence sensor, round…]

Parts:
C1: 22uF; C_0805_2012Metric
C2: 4.7uF; C_0603_1608Metric
C3, C4, C7: 10uF; C_0805_2012Metric
C5, C8: 100nF; C_0603_1608Metric
C6: 1uF; C_0603_1608Metric
D1: SMF5.0A; D_SOD-123F
F1: PTC 0.5A; Fuse_0805_2012Metric
J1: USB-C 6P (power only); USB_C_Receptacle_GCT_USB4135-GF-A_6P_TopMnt_Horizontal
R1, R2: 5.1k; R_0402_1005Metric
R3, R4, R5, R6: 10k; R_0603_1608Metric
R7: 100k; R_0603_1608Metric
RD1: HLK-LD2410C; HLK-LD2410C_1x05_P2.54mm
SW1: RESET; SW_SPST_B3U-1000P
TP1: 3V3; TestPoint_Pad_D1.4mm_Tight
TP2: EN; TestPoint_Pad_D1.4mm_Tight
TP3: GND; TestPoint_Pad_D1.4mm_Tight
TP4: IO9; TestPoint_Pad_D1.4mm_Tight
TP5: RX0; TestPoint_Pad_D1.4mm_Tight
TP6: TX0; TestPoint_Pad_D1.4mm_Tight
U1: ESP32-C3-WROOM-02-N4; ESP32-C3-WROOM-02
U2: AP2112K-3.3; SOT-23-5

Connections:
+3V3: C3.1, C4.2, C5.2, R3.1, R4.1, R5.1, R6.1, TP1.1, U1.1 (3V3), U2.5 (VOUT)
+5V: C1.1, C2.1, C7.1, C8.1, D1.1 (K), F1.2, RD1.5 (VCC), U2.1 (VIN), U2.3 (EN)
/CC1: J1.A5 (CC1), R1.1
/CC2: J1.B5 (CC2), R2.1
/EN: C6.1, R3.2, SW1.1, TP2.1, U1.2 (EN)
/IO2: R6.2, U1.16 (IO2)
/IO8: R5.2, U1.7 (IO8)
/IO9: R4.2, TP4.1, U1.8 (IO9)
/RADAR_OUT: R7.1, RD1.3 (OUT), U1.17 (IO1)
/RADAR_RX: RD1.2 (RX), U1.15 (IO3)
/RADAR_TX: RD1.1 (TX), U1.10 (IO10)
/RXD0: TP5.1, U1.11 (RXD0/IO20)
/TXD0: TP6.1, U1.12 (TXD0/IO21)
GND: C1.2, C2.2, C3.2, C4.1, C5.1, C6.2, C7.2, C8.2, D1.2 (A), J1.A12 (GND), J1.B12 (GND), J1.S1 (SHIELD), R1.2, R2.2, R7.2, RD1.4 (GND), SW1.2, TP3.1, U1.9 (GND), U1.19 (GND), U2.2 (GND)
VBUS: F1.1, J1.A9 (VBUS), J1.B9 (VBUS)

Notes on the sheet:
1. USB-C 5 V input (power only)
Power flags
2. Protection + 3.3 V LDO
3. HLK-LD2410C radar (beside U1, antenna face up)
4. ESP32-C3-WROOM-02-N4
5. Reset / boot / strapping
6. Programming pads (pogo / solder, bottom side)
NOTES 1. Round PCB D45 mm, 2 layers, 1.6 mm. U1, RD1, C4, C5 on the top (room side); everything else on the bottom. 2. RD1 (HLK-LD2410C) sits flat below U1, not stacked: header insulator on the PCB, antenna face up, about 16 mm from the WiFi antenna zone. Solder the 5 pins from the bottom and trim 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
